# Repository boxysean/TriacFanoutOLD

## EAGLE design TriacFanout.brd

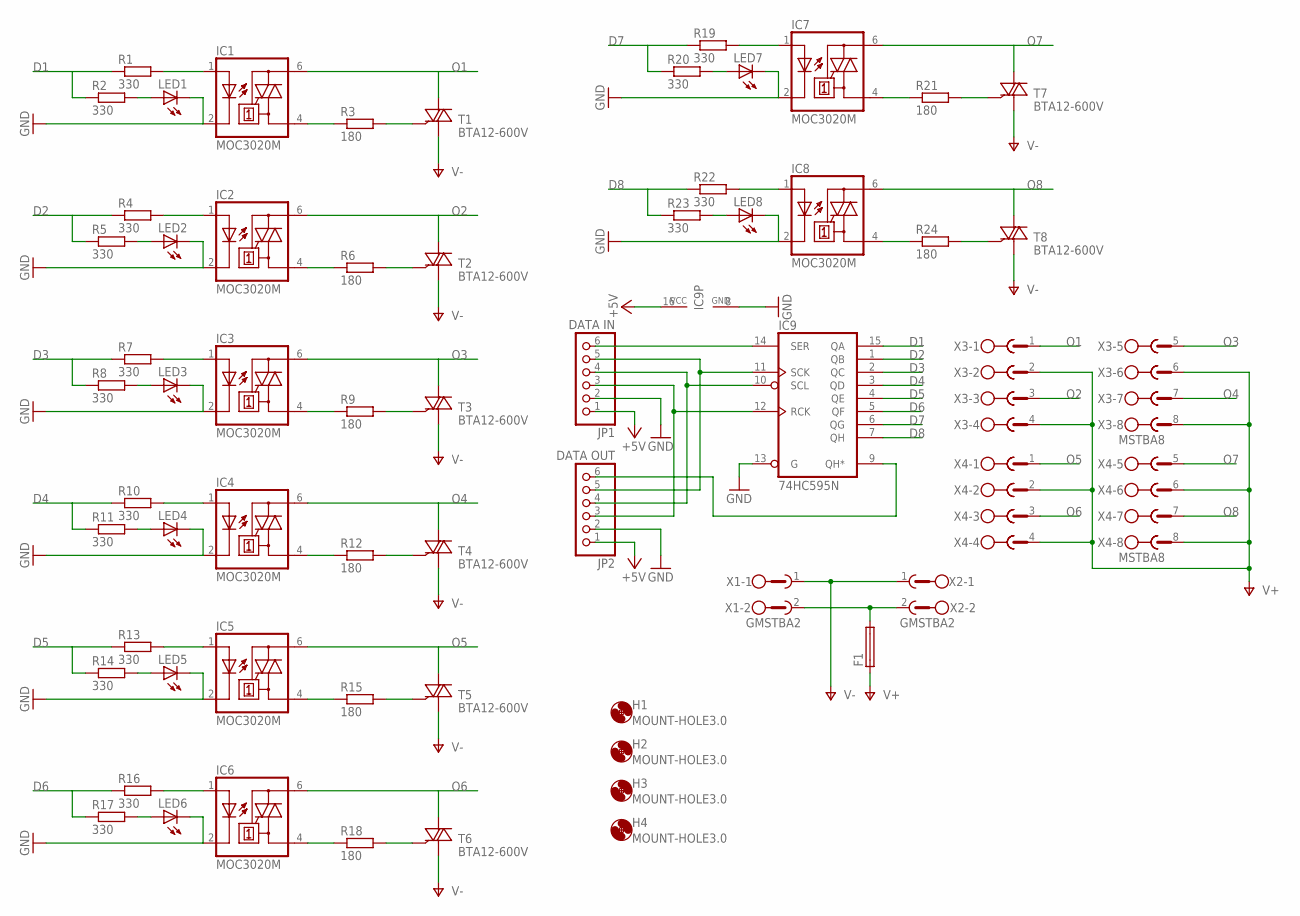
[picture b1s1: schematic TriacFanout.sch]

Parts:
F1: SH22,5
H1, H2, H3, H4: MOUNT-HOLE3.0; 3,0
IC1, IC2, IC3, IC4, IC5, IC6, IC7, IC8: MOC3020M; DIL06
IC9: 74HC595N; DIL16
JP1: DATA IN; 1X06
JP2: DATA OUT; 1X06
LED1, LED2, LED3, LED4, LED5, LED6, LED7, LED8: LED5MM
R1, R2, R4, R5, R7, R8, R10, R11, R13, R14, R16, R17, R19, R20, R22, R23: 330; 0204/7
R3, R6, R9, R12, R15, R18, R21, R24: 180; 0204/7
T1, T2, T3, T4, T5, T6, T7, T8: BTA12-600V; TO220V
X1, X2: GMSTBA2
X3, X4: MSTBA8

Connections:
+5V: IC9.16 (VCC), JP1.1, JP2.1
D1: IC9.15 (QA), R1.1, R2.1
D2: IC9.1 (QB), R4.1, R5.1
D3: IC9.2 (QC), R7.1, R8.1
D4: IC9.3 (QD), R10.1, R11.1
D5: IC9.4 (QE), R13.1, R14.1
D6: IC9.5 (QF), R16.1, R17.1
D7: IC9.6 (QG), R19.1, R20.1
D8: IC9.7 (QH), R22.1, R23.1
GND: IC1.2 (C), IC2.2 (C), IC3.2 (C), IC4.2 (C), IC5.2 (C), IC6.2 (C), IC7.2 (C), IC8.2 (C), IC9.8 (GND), IC9.13 (G), JP1.2, JP2.2, LED1.K (C), LED2.K (C), LED3.K (C), LED4.K (C), LED5.K (C), LED6.K (C), LED7.K (C), LED8.K (C)
unnamed: IC2.1 (A), R4.2
unnamed: LED2.A, R5.2
unnamed: IC2.4 (A1), R6.1
unnamed: R6.2, T2.3 (G)
unnamed: IC3.1 (A), R7.2
unnamed: LED3.A, R8.2
unnamed: IC3.4 (A1), R9.1
unnamed: R9.2, T3.3 (G)
unnamed: IC1.4 (A1), R3.1
unnamed: IC1.1 (A), R1.2
unnamed: R3.2, T1.3 (G)
unnamed: LED1.A, R2.2
unnamed: IC4.1 (A), R10.2
unnamed: LED4.A, R11.2
unnamed: IC4.4 (A1), R12.1
unnamed: R12.2, T4.3 (G)
unnamed: IC5.1 (A), R13.2
unnamed: LED5.A, R14.2
unnamed: IC5.4 (A1), R15.1
unnamed: R15.2, T5.3 (G)
unnamed: IC6.1 (A), R16.2
unnamed: LED6.A, R17.2
unnamed: IC6.4 (A1), R18.1
unnamed: R18.2, T6.3 (G)
unnamed: IC7.1 (A), R19.2
unnamed: LED7.A, R20.2
unnamed: IC7.4 (A1), R21.1
unnamed: R21.2, T7.3 (G)
unnamed: IC8.1 (A), R22.2
unnamed: LED8.A, R23.2
unnamed: IC8.4 (A1), R24.1
unnamed: R24.2, T8.3 (G)
unnamed: F1.2, X1.2, X2.2
unnamed: IC9.14 (SER), JP1.6
unnamed: IC9.9 (QH*), JP2.6
unnamed: IC9.11 (SCK), JP1.5, JP2.5
unnamed: IC9.10 (SCL), JP1.4, JP2.4
unnamed: IC9.12 (RCK), JP1.3, JP2.3
O1: IC1.6 (A2), T1.2 (A2), X3.1
O2: IC2.6 (A2), T2.2 (A2), X3.3
O3: IC3.6 (A2), T3.2 (A2), X3.5
O4: IC4.6 (A2), T4.2 (A2), X3.7
O5: IC5.6 (A2), T5.2 (A2), X4.1
O6: IC6.6 (A2), T6.2 (A2), X4.3
O7: IC7.6 (A2), T7.2 (A2), X4.5
O8: IC8.6 (A2), T8.2 (A2), X4.7
V+: F1.1, X3.2, X3.4, X3.6, X3.8, X4.2, X4.4, X4.6, X4.8
V-: T1.1 (A1), T2.1 (A1), T3.1 (A1), T4.1 (A1), T5.1 (A1), T6.1 (A1), T7.1 (A1), T8.1 (A1), X1.1, X2.1

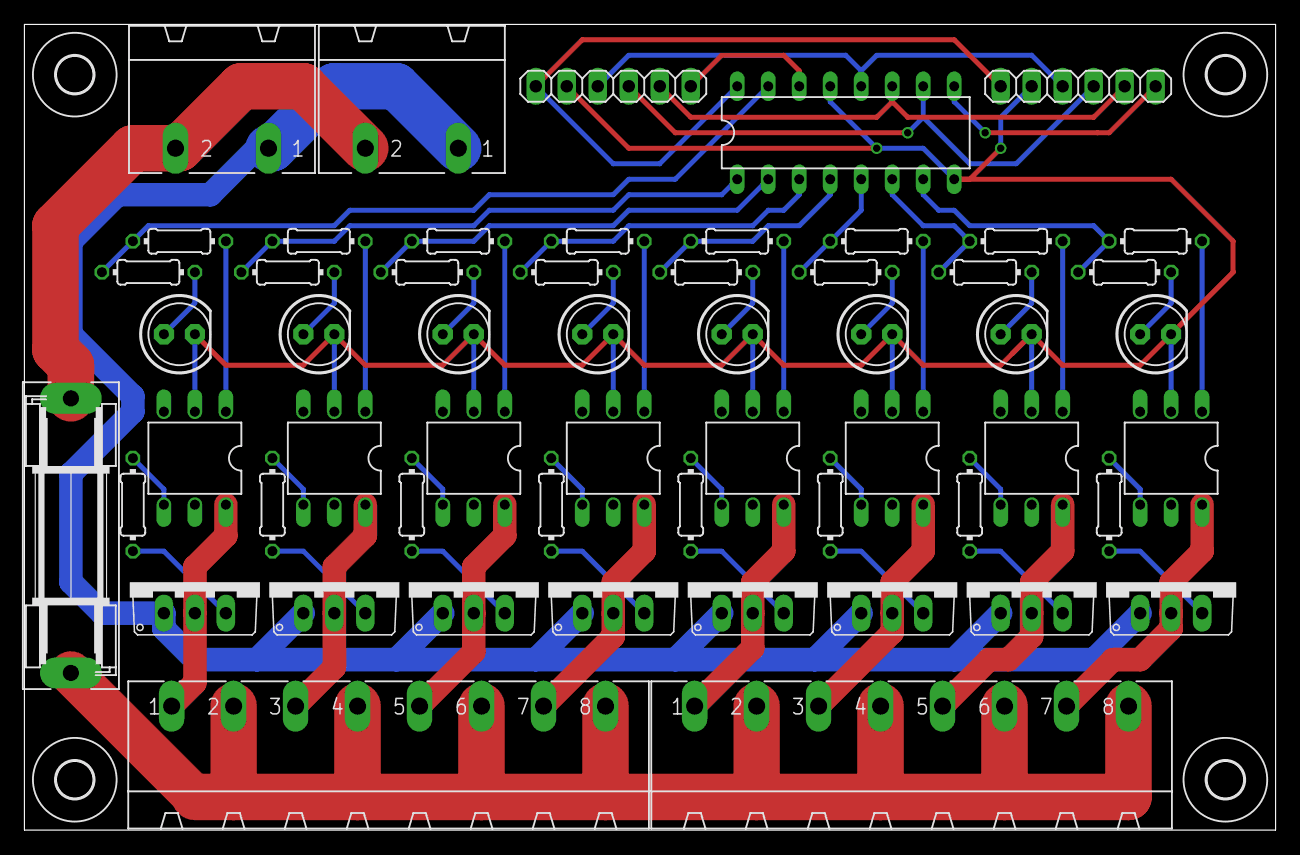
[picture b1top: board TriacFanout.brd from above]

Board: 2 copper layers, 102.5 x 66.0 mm, 60 parts (0 on the bottom side), 58 nets.

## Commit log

2014-04-27 images!
2014-08-07 added triacfanout
